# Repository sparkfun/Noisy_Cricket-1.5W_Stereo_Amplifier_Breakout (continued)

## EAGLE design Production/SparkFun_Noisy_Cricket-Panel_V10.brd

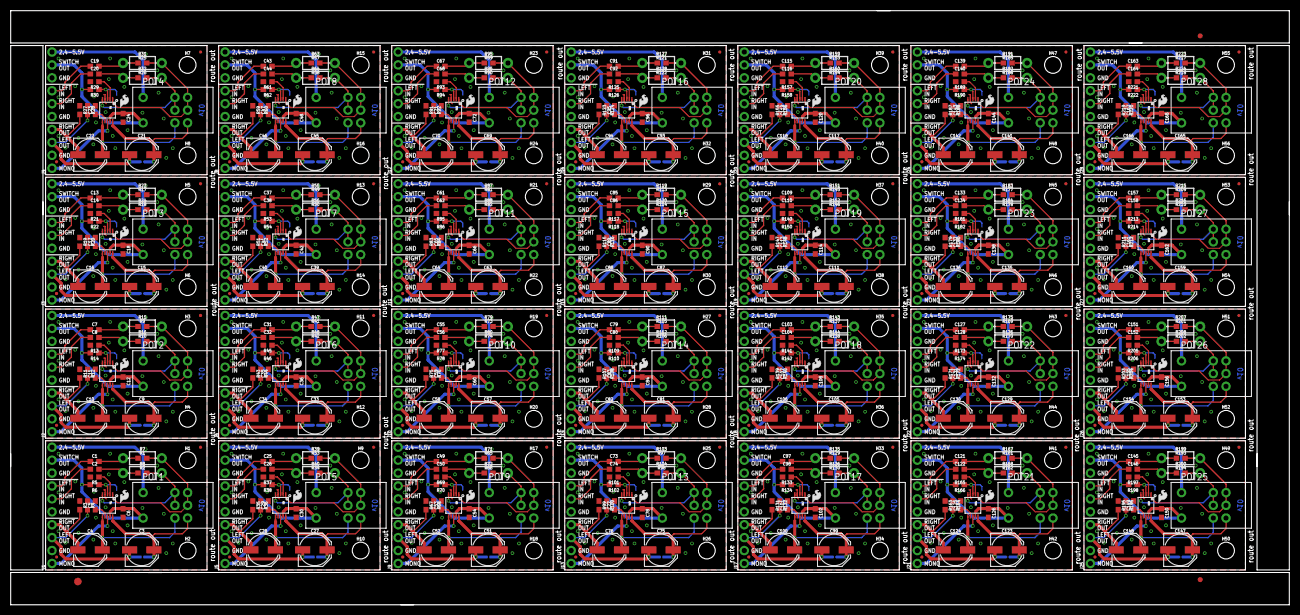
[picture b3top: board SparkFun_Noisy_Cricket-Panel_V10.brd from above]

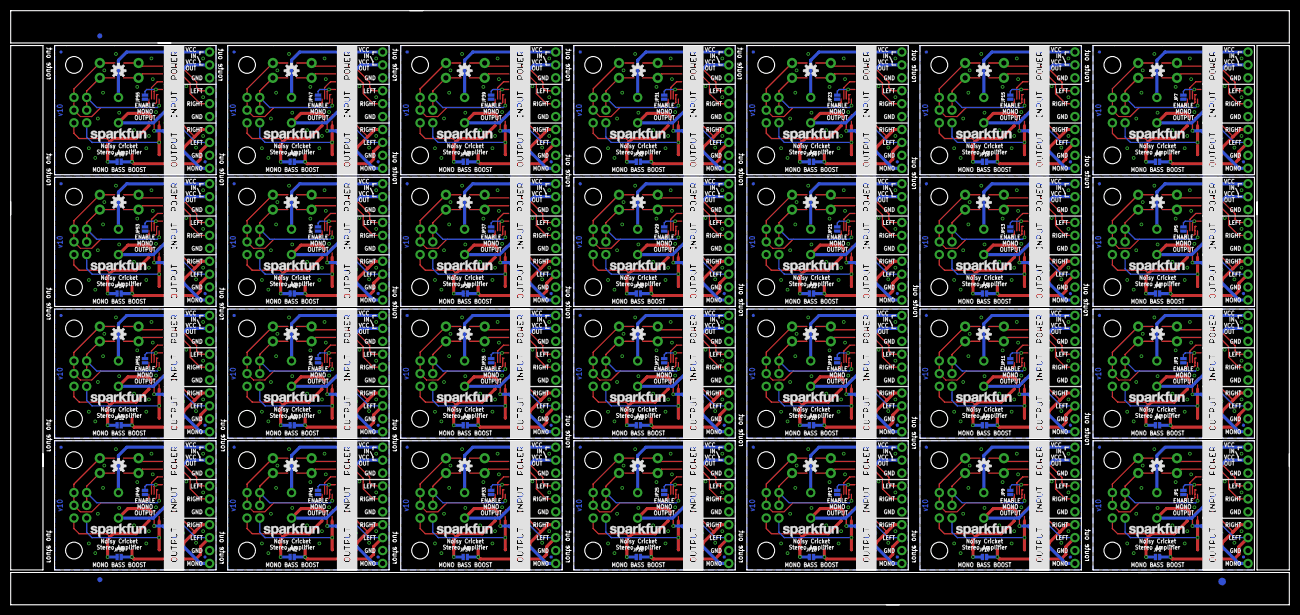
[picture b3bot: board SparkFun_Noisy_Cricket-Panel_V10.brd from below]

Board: 2 copper layers, 251.5 x 116.8 mm, 790 parts (171 on the bottom side), 476 nets.

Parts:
C1, C2, C5, C6, C7, C8, C11, C12, C13, C14, C17, C18, C19, C20, C23, C24, C25, C26, C29, C30, C31, C32, C35, C36, C37, C38, C41, C42, C43, C44, C47, C48, C49, C50, C53, C54, C55, C56, C59, C60, C61, C62, C65, C66, C67, C68, C71, C72, C73, C74, C77, C78, C79, C80, C83, C84, C85, C86, C89, C90, C91, C92, C95, C96, C97, C98, C101, C102, C103, C104, C107, C108, C109, C110, C113, C114, C115, C116, C119, C120, C121, C122, C125, C126, C127, C128, C131, C132, C133, C134, C137, C138, C139, C140, C143, C144, C145, C146, C149, C150, C151, C152, C155, C156, C157, C158, C161, C162, C163, C164, C167, C168: 1.0uF; 0603
C3, C4, C9, C10, C15, C16, C21, C22, C27, C28, C33, C34, C39, C40, C45, C46, C51, C52, C57, C58, C63, C64, C69, C70, C75, C76, C81, C82, C87, C88, C93, C94, C99, C100, C105, C106, C111, C112, C117, C118, C123, C124, C129, C130, C135, C136, C141, C142, C147, C148, C153, C154, C159, C160, C165, C166: 100uF; PANASONIC_D
E$1, E$2: FIDUCIAL-1.5X3
E$3, E$4, E$5, E$7: FIDUCIAL-1X2
FD1, FD2, FD3, FD4, FD5, FD6, FD7, FD8, FD9, FD10, FD11, FD12, FD13, FD14, FD15, FD16, FD17, FD18, FD19, FD20, FD21, FD22, FD23, FD24, FD25, FD26, FD27, FD28, FD29, FD30, FD31, FD32, FD33, FD34, FD35, FD36, FD37, FD38, FD39, FD40, FD41, FD42, FD43, FD44, FD45, FD46, FD47, FD48, FD49, FD50, FD51, FD52, FD53, FD54, FD55, FD56, FD57, FD58, FD59, FD60, FD61, FD62, FD63, FD64, FD65, FD66, FD67, FD68, FD69, FD70, FD71, FD72, FD73, FD74, FD75, FD76, FD77, FD78, FD79, FD80, FD81, FD82, FD83, FD84, FD85, FD86, FD87, FD88, FD89, FD90, FD91, FD92, FD93, FD94, FD95, FD96, FD97, FD98, FD99, FD100, FD101, FD102, FD103, FD104, FD105, FD106, FD107, FD108, FD109, FD110, FD111, FD112: FIDUCIALUFIDUCIAL; FIDUCIAL-MICRO
H1, H2, H3, H4, H5, H6, H7, H8, H9, H10, H11, H12, H13, H14, H15, H16, H17, H18, H19, H20, H21, H22, H23, H24, H25, H26, H27, H28, H29, H30, H31, H32, H33, H34, H35, H36, H37, H38, H39, H40, H41, H42, H43, H44, H45, H46, H47, H48, H49, H50, H51, H52, H53, H54, H55, H56: STAND-OFF
J1, J2, J3, J4, J5, J6, J7, J8, J9, J10, J11, J12, J13, J14, J15, J16, J17, J18, J19, J20, J21, J22, J23, J24, J25, J26, J27, J28: 1X10_NO_SILK
JP1, JP2, JP3, JP4, JP5, JP6, JP7, JP8, JP9, JP10, JP11, JP12, JP13, JP14, JP15, JP16, JP17, JP18, JP19, JP20, JP21, JP22, JP23, JP24, JP25, JP26, JP27, JP28, JP29, JP30, JP31, JP32, JP33, JP34, JP35, JP36, JP37, JP38, JP39, JP40, JP41, JP42, JP43, JP44, JP45, JP46, JP47, JP48, JP49, JP50, JP51, JP52, JP53, JP54, JP55, JP56: SMT-JUMPER_2_NO_NO-SILK
LOGO1, LOGO3, LOGO5, LOGO7, LOGO9, LOGO11, LOGO13, LOGO15, LOGO17, LOGO19, LOGO21, LOGO23, LOGO25, LOGO27, LOGO29, LOGO31, LOGO33, LOGO35, LOGO37, LOGO39, LOGO41, LOGO43, LOGO45, LOGO47, LOGO49, LOGO51, LOGO53, LOGO55: SFE_LOGO_NAME.1_INCH; SFE_LOGO_NAME_.1
LOGO2, LOGO4, LOGO6, LOGO8, LOGO10, LOGO12, LOGO14, LOGO16, LOGO18, LOGO20, LOGO22, LOGO24, LOGO26, LOGO28, LOGO30, LOGO32, LOGO34, LOGO36, LOGO38, LOGO40, LOGO42, LOGO44, LOGO46, LOGO48, LOGO50, LOGO52, LOGO54, LOGO56: OSHW-LOGOS; OSHW-LOGO-S
POT1, POT2, POT3, POT4, POT5, POT6, POT7, POT8, POT9, POT10, POT11, POT12, POT13, POT14, POT15, POT16, POT17, POT18, POT19, POT20, POT21, POT22, POT23, POT24, POT25, POT26, POT27, POT28: 20k; POT-DUAL-SWITCH-PTH
R1, R2, R9, R10, R17, R18, R25, R26, R33, R34, R41, R42, R49, R50, R57, R58, R65, R66, R73, R74, R81, R82, R89, R90, R97, R98, R105, R106, R113, R114, R121, R122, R129, R130, R137, R138, R145, R146, R153, R154, R161, R162, R169, R170, R177, R178, R185, R186, R193, R194, R201, R202, R209, R210, R217, R218: 2.2k; 0603
R3, R4, R11, R12, R19, R20, R27, R28, R35, R36, R43, R44, R51, R52, R59, R60, R67, R68, R75, R76, R83, R84, R91, R92, R99, R100, R107, R108, R115, R116, R123, R124, R131, R132, R139, R140, R147, R148, R155, R156, R163, R164, R171, R172, R179, R180, R187, R188, R195, R196, R203, R204, R211, R212, R219, R220: 1k; 0603
R5, R6, R13, R14, R21, R22, R29, R30, R37, R38, R45, R46, R53, R54, R61, R62, R69, R70, R77, R78, R85, R86, R93, R94, R101, R102, R109, R110, R117, R118, R125, R126, R133, R134, R141, R142, R149, R150, R157, R158, R165, R166, R173, R174, R181, R182, R189, R190, R197, R198, R205, R206, R213, R214, R221, R222: 100k; 0603
R7, R8, R15, R16, R23, R24, R31, R32, R39, R40, R47, R48, R55, R56, R63, R64, R71, R72, R79, R80, R87, R88, R95, R96, R103, R104, R111, R112, R119, R120, R127, R128, R135, R136, R143, R144, R151, R152, R159, R160, R167, R168, R175, R176, R183, R184, R191, R192, R199, R200, R207, R208, R215, R216, R223, R224: AXIAL-0.3-KIT
U1, U2, U3, U4, U5, U6, U7, U8, U9, U10, U11, U12, U13, U14, U15, U16, U17, U18, U19, U20, U21, U22, U23, U24, U25, U26, U27, U28: LM4853; TFSOP-10
U$1, U$2, U$3, U$4, U$5, U$6, U$7, U$8, U$9, U$10, U$11, U$12, U$13, U$14, U$15, U$16, U$17, U$18, U$19, U$20, U$21, U$22, U$23, U$24, U$25, U$26, U$27, U$28: SFE_LOGO_FLAME_.1

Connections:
5V: C6.1, J1.9, POT1.SW2, R6.2, U1.VDD
5V1: C12.1, J2.9, POT2.SW2, R14.2, U2.VDD
5V2: C18.1, J3.9, POT3.SW2, R22.2, U3.VDD
5V3: C24.1, J4.9, POT4.SW2, R30.2, U4.VDD
5V4: C30.1, J5.9, POT5.SW2, R38.2, U5.VDD
5V5: C36.1, J6.9, POT6.SW2, R46.2, U6.VDD
5V6: C42.1, J7.9, POT7.SW2, R54.2, U7.VDD
5V7: C48.1, J8.9, POT8.SW2, R62.2, U8.VDD
5V8: C54.1, J9.9, POT9.SW2, R70.2, U9.VDD
5V9: C60.1, J10.9, POT10.SW2, R78.2, U10.VDD
5V10: C66.1, J11.9, POT11.SW2, R86.2, U11.VDD
5V11: C72.1, J12.9, POT12.SW2, R94.2, U12.VDD
5V12: C78.1, J13.9, POT13.SW2, R102.2, U13.VDD
5V13: C84.1, J14.9, POT14.SW2, R110.2, U14.VDD
5V14: C90.1, J15.9, POT15.SW2, R118.2, U15.VDD
5V15: C96.1, J16.9, POT16.SW2, R126.2, U16.VDD
5V16: C102.1, J17.9, POT17.SW2, R134.2, U17.VDD
5V17: C108.1, J18.9, POT18.SW2, R142.2, U18.VDD
5V18: C114.1, J19.9, POT19.SW2, R150.2, U19.VDD
5V19: C120.1, J20.9, POT20.SW2, R158.2, U20.VDD
5V20: C126.1, J21.9, POT21.SW2, R166.2, U21.VDD
5V21: C132.1, J22.9, POT22.SW2, R174.2, U22.VDD
5V22: C138.1, J23.9, POT23.SW2, R182.2, U23.VDD
5V23: C144.1, J24.9, POT24.SW2, R190.2, U24.VDD
5V24: C150.1, J25.9, POT25.SW2, R198.2, U25.VDD
5V25: C156.1, J26.9, POT26.SW2, R206.2, U26.VDD
5V26: C162.1, J27.9, POT27.SW2, R214.2, U27.VDD
5V27: C168.1, J28.9, POT28.SW2, R222.2, U28.VDD
GND: C5.2, C6.2, J1.2, J1.5, J1.8, JP1.1, R3.1, R4.1, R5.2, U1.GND
GND1: C11.2, C12.2, J2.2, J2.5, J2.8, JP3.1, R11.1, R12.1, R13.2, U2.GND
GND2: C17.2, C18.2, J3.2, J3.5, J3.8, JP5.1, R19.1, R20.1, R21.2, U3.GND
GND3: C23.2, C24.2, J4.2, J4.5, J4.8, JP7.1, R27.1, R28.1, R29.2, U4.GND
GND4: C29.2, C30.2, J5.2, J5.5, J5.8, JP9.1, R35.1, R36.1, R37.2, U5.GND
GND5: C35.2, C36.2, J6.2, J6.5, J6.8, JP11.1, R43.1, R44.1, R45.2, U6.GND
GND6: C41.2, C42.2, J7.2, J7.5, J7.8, JP13.1, R51.1, R52.1, R53.2, U7.GND
GND7: C47.2, C48.2, J8.2, J8.5, J8.8, JP15.1, R59.1, R60.1, R61.2, U8.GND
GND8: C53.2, C54.2, J9.2, J9.5, J9.8, JP17.1, R67.1, R68.1, R69.2, U9.GND
GND9: C59.2, C60.2, J10.2, J10.5, J10.8, JP19.1, R75.1, R76.1, R77.2, U10.GND
GND10: C65.2, C66.2, J11.2, J11.5, J11.8, JP21.1, R83.1, R84.1, R85.2, U11.GND
GND11: C71.2, C72.2, J12.2, J12.5, J12.8, JP23.1, R91.1, R92.1, R93.2, U12.GND
GND12: C77.2, C78.2, J13.2, J13.5, J13.8, JP25.1, R99.1, R100.1, R101.2, U13.GND
GND13: C83.2, C84.2, J14.2, J14.5, J14.8, JP27.1, R107.1, R108.1, R109.2, U14.GND
GND14: C89.2, C90.2, J15.2, J15.5, J15.8, JP29.1, R115.1, R116.1, R117.2, U15.GND
GND15: C95.2, C96.2, J16.2, J16.5, J16.8, JP31.1, R123.1, R124.1, R125.2, U16.GND
GND16: C101.2, C102.2, J17.2, J17.5, J17.8, JP33.1, R131.1, R132.1, R133.2, U17.GND
GND17: C107.2, C108.2, J18.2, J18.5, J18.8, JP35.1, R139.1, R140.1, R141.2, U18.GND
GND18: C113.2, C114.2, J19.2, J19.5, J19.8, JP37.1, R147.1, R148.1, R149.2, U19.GND
GND19: C119.2, C120.2, J20.2, J20.5, J20.8, JP39.1, R155.1, R156.1, R157.2, U20.GND
GND20: C125.2, C126.2, J21.2, J21.5, J21.8, JP41.1, R163.1, R164.1, R165.2, U21.GND
GND21: C131.2, C132.2, J22.2, J22.5, J22.8, JP43.1, R171.1, R172.1, R173.2, U22.GND
GND22: C137.2, C138.2, J23.2, J23.5, J23.8, JP45.1, R179.1, R180.1, R181.2, U23.GND
GND23: C143.2, C144.2, J24.2, J24.5, J24.8, JP47.1, R187.1, R188.1, R189.2, U24.GND
GND24: C149.2, C150.2, J25.2, J25.5, J25.8, JP49.1, R195.1, R196.1, R197.2, U25.GND
GND25: C155.2, C156.2, J26.2, J26.5, J26.8, JP51.1, R203.1, R204.1, R205.2, U26.GND
GND26: C161.2, C162.2, J27.2, J27.5, J27.8, JP53.1, R211.1, R212.1, R213.2, U27.GND
GND27: C167.2, C168.2, J28.2, J28.5, J28.8, JP55.1, R219.1, R220.1, R221.2, U28.GND
LIN: C1.1, J1.7
LIN1: C7.1, J2.7
LIN2: C13.1, J3.7
LIN3: C19.1, J4.7
LIN4: C25.1, J5.7
LIN5: C31.1, J6.7
LIN6: C37.1, J7.7
LIN7: C43.1, J8.7
LIN8: C49.1, J9.7
LIN9: C55.1, J10.7
LIN10: C61.1, J11.7
LIN11: C67.1, J12.7
LIN12: C73.1, J13.7
LIN13: C79.1, J14.7
LIN14: C85.1, J15.7
LIN15: C91.1, J16.7
LIN16: C97.1, J17.7
LIN17: C103.1, J18.7
LIN18: C109.1, J19.7
LIN19: C115.1, J20.7
LIN20: C121.1, J21.7
LIN21: C127.1, J22.7
LIN22: C133.1, J23.7
LIN23: C139.1, J24.7
LIN24: C145.1, J25.7
LIN25: C151.1, J26.7
LIN26: C157.1, J27.7
LIN27: C163.1, J28.7
LOUT: C3.-, J1.3, JP2.2, R4.2
LOUT1: C9.-, J2.3, JP4.2, R12.2
LOUT2: C15.-, J3.3, JP6.2, R20.2
LOUT3: C21.-, J4.3, JP8.2, R28.2
LOUT4: C27.-, J5.3, JP10.2, R36.2
LOUT5: C33.-, J6.3, JP12.2, R44.2
LOUT6: C39.-, J7.3, JP14.2, R52.2
LOUT7: C45.-, J8.3, JP16.2, R60.2
LOUT8: C51.-, J9.3, JP18.2, R68.2
LOUT9: C57.-, J10.3, JP20.2, R76.2
LOUT10: C63.-, J11.3, JP22.2, R84.2
LOUT11: C69.-, J12.3, JP24.2, R92.2
LOUT12: C75.-, J13.3, JP26.2, R100.2
LOUT13: C81.-, J14.3, JP28.2, R108.2
LOUT14: C87.-, J15.3, JP30.2, R116.2
LOUT15: C93.-, J16.3, JP32.2, R124.2
LOUT16: C99.-, J17.3, JP34.2, R132.2
LOUT17: C105.-, J18.3, JP36.2, R140.2
LOUT18: C111.-, J19.3, JP38.2, R148.2
LOUT19: C117.-, J20.3, JP40.2, R156.2
LOUT20: C123.-, J21.3, JP42.2, R164.2
LOUT21: C129.-, J22.3, JP44.2, R172.2
LOUT22: C135.-, J23.3, JP46.2, R180.2
LOUT23: C141.-, J24.3, JP48.2, R188.2
LOUT24: C147.-, J25.3, JP50.2, R196.2
LOUT25: C153.-, J26.3, JP52.2, R204.2
LOUT26: C159.-, J27.3, JP54.2, R212.2
LOUT27: C165.-, J28.3, JP56.2, R220.2
LOUT+: C3.+, JP2.1, POT1.A3, U1.LOUT
LOUT+1: C9.+, JP4.1, POT2.A3, U2.LOUT
LOUT+2: C15.+, JP6.1, POT3.A3, U3.LOUT
LOUT+3: C21.+, JP8.1, POT4.A3, U4.LOUT
LOUT+4: C27.+, JP10.1, POT5.A3, U5.LOUT
LOUT+5: C33.+, JP12.1, POT6.A3, U6.LOUT
LOUT+6: C39.+, JP14.1, POT7.A3, U7.LOUT
LOUT+7: C45.+, JP16.1, POT8.A3, U8.LOUT
LOUT+8: C51.+, JP18.1, POT9.A3, U9.LOUT
LOUT+9: C57.+, JP20.1, POT10.A3, U10.LOUT
LOUT+10: C63.+, JP22.1, POT11.A3, U11.LOUT
LOUT+11: C69.+, JP24.1, POT12.A3, U12.LOUT
LOUT+12: C75.+, JP26.1, POT13.A3, U13.LOUT
LOUT+13: C81.+, JP28.1, POT14.A3, U14.LOUT
LOUT+14: C87.+, JP30.1, POT15.A3, U15.LOUT
LOUT+15: C93.+, JP32.1, POT16.A3, U16.LOUT
LOUT+16: C99.+, JP34.1, POT17.A3, U17.LOUT
LOUT+17: C105.+, JP36.1, POT18.A3, U18.LOUT
LOUT+18: C111.+, JP38.1, POT19.A3, U19.LOUT
LOUT+19: C117.+, JP40.1, POT20.A3, U20.LOUT
LOUT+20: C123.+, JP42.1, POT21.A3, U21.LOUT
LOUT+21: C129.+, JP44.1, POT22.A3, U22.LOUT
LOUT+22: C135.+, JP46.1, POT23.A3, U23.LOUT
LOUT+23: C141.+, JP48.1, POT24.A3, U24.LOUT
LOUT+24: C147.+, JP50.1, POT25.A3, U25.LOUT
LOUT+25: C153.+, JP52.1, POT26.A3, U26.LOUT
LOUT+26: C159.+, JP54.1, POT27.A3, U27.LOUT
LOUT+27: C165.+, JP56.1, POT28.A3, U28.LOUT
MODE: JP1.2, R6.1, U1.HP-IN
MODE1: JP3.2, R14.1, U2.HP-IN
MODE2: JP5.2, R22.1, U3.HP-IN
MODE3: JP7.2, R30.1, U4.HP-IN
MODE4: JP9.2, R38.1, U5.HP-IN
MODE5: JP11.2, R46.1, U6.HP-IN
MODE6: JP13.2, R54.1, U7.HP-IN
MODE7: JP15.2, R62.1, U8.HP-IN
MODE8: JP17.2, R70.1, U9.HP-IN
MODE9: JP19.2, R78.1, U10.HP-IN
MODE10: JP21.2, R86.1, U11.HP-IN
MODE11: JP23.2, R94.1, U12.HP-IN
MODE12: JP25.2, R102.1, U13.HP-IN
MODE13: JP27.2, R110.1, U14.HP-IN
MODE14: JP29.2, R118.1, U15.HP-IN
MODE15: JP31.2, R126.1, U16.HP-IN
MODE16: JP33.2, R134.1, U17.HP-IN
MODE17: JP35.2, R142.1, U18.HP-IN
MODE18: JP37.2, R150.1, U19.HP-IN
MODE19: JP39.2, R158.1, U20.HP-IN
MODE20: JP41.2, R166.1, U21.HP-IN
MODE21: JP43.2, R174.1, U22.HP-IN
MODE22: JP45.2, R182.1, U23.HP-IN
MODE23: JP47.2, R190.1, U24.HP-IN
MODE24: JP49.2, R198.1, U25.HP-IN
MODE25: JP51.2, R206.1, U26.HP-IN
MODE26: JP53.2, R214.1, U27.HP-IN
MODE27: JP55.2, R222.1, U28.HP-IN
MONO_OUT: J1.1, U1.BTL
MONO_OUT1: J2.1, U2.BTL
MONO_OUT2: J3.1, U3.BTL
MONO_OUT3: J4.1, U4.BTL
MONO_OUT4: J5.1, U5.BTL
MONO_OUT5: J6.1, U6.BTL
MONO_OUT6: J7.1, U7.BTL
MONO_OUT7: J8.1, U8.BTL
MONO_OUT8: J9.1, U9.BTL
MONO_OUT9: J10.1, U10.BTL
MONO_OUT10: J11.1, U11.BTL
MONO_OUT11: J12.1, U12.BTL
MONO_OUT12: J13.1, U13.BTL
MONO_OUT13: J14.1, U14.BTL
MONO_OUT14: J15.1, U15.BTL
MONO_OUT15: J16.1, U16.BTL
MONO_OUT16: J17.1, U17.BTL
MONO_OUT17: J18.1, U18.BTL
MONO_OUT18: J19.1, U19.BTL
MONO_OUT19: J20.1, U20.BTL
MONO_OUT20: J21.1, U21.BTL
MONO_OUT21: J22.1, U22.BTL
MONO_OUT22: J23.1, U23.BTL
MONO_OUT23: J24.1, U24.BTL
MONO_OUT24: J25.1, U25.BTL
MONO_OUT25: J26.1, U26.BTL
MONO_OUT26: J27.1, U27.BTL
MONO_OUT27: J28.1, U28.BTL
unnamed: C7.2, R9.1, R15.P$1
unnamed: R13.1, U2.SDN
unnamed: C1.2, R1.1, R7.P$1
unnamed: C11.1, U2.BP
unnamed: C5.1, U1.BP
unnamed: C2.2, R2.1, R8.P$1
unnamed: C10.+, POT2.B3, U2.ROUT
unnamed: POT2.A1, POT2.A2, R9.2, R15.P$2, U2.LIN
unnamed: R5.1, U1.SDN
unnamed: POT2.B1, POT2.B2, R10.2, R16.P$2, U2.RIN
unnamed: C8.2, R10.1, R16.P$1
unnamed: C4.+, POT1.B3, U1.ROUT
unnamed: C13.2, R17.1, R23.P$1
unnamed: R21.1, U3.SDN
unnamed: C17.1, U3.BP
unnamed: C16.+, POT3.B3, U3.ROUT
unnamed: POT3.A1, POT3.A2, R17.2, R23.P$2, U3.LIN
unnamed: POT3.B1, POT3.B2, R18.2, R24.P$2, U3.RIN
unnamed: C14.2, R18.1, R24.P$1
unnamed: C19.2, R25.1, R31.P$1
unnamed: POT1.A1, POT1.A2, R1.2, R7.P$2, U1.LIN
unnamed: R29.1, U4.SDN
unnamed: C23.1, U4.BP
unnamed: POT1.B1, POT1.B2, R2.2, R8.P$2, U1.RIN
unnamed: C22.+, POT4.B3, U4.ROUT
unnamed: POT4.A1, POT4.A2, R25.2, R31.P$2, U4.LIN
unnamed: POT4.B1, POT4.B2, R26.2, R32.P$2, U4.RIN
unnamed: C20.2, R26.1, R32.P$1
unnamed: C25.2, R33.1, R39.P$1
unnamed: R37.1, U5.SDN
unnamed: C29.1, U5.BP
unnamed: C28.+, POT5.B3, U5.ROUT
unnamed: POT5.A1, POT5.A2, R33.2, R39.P$2, U5.LIN
unnamed: POT5.B1, POT5.B2, R34.2, R40.P$2, U5.RIN
unnamed: C26.2, R34.1, R40.P$1
unnamed: C31.2, R41.1, R47.P$1
unnamed: R45.1, U6.SDN
unnamed: C35.1, U6.BP
unnamed: C34.+, POT6.B3, U6.ROUT
unnamed: POT6.A1, POT6.A2, R41.2, R47.P$2, U6.LIN
unnamed: POT6.B1, POT6.B2, R42.2, R48.P$2, U6.RIN
unnamed: C32.2, R42.1, R48.P$1
unnamed: C37.2, R49.1, R55.P$1
unnamed: R53.1, U7.SDN
unnamed: C41.1, U7.BP
unnamed: C40.+, POT7.B3, U7.ROUT
unnamed: POT7.A1, POT7.A2, R49.2, R55.P$2, U7.LIN
unnamed: POT7.B1, POT7.B2, R50.2, R56.P$2, U7.RIN
unnamed: C38.2, R50.1, R56.P$1
unnamed: C43.2, R57.1, R63.P$1
unnamed: R61.1, U8.SDN
unnamed: C47.1, U8.BP
unnamed: C46.+, POT8.B3, U8.ROUT
unnamed: POT8.A1, POT8.A2, R57.2, R63.P$2, U8.LIN
unnamed: POT8.B1, POT8.B2, R58.2, R64.P$2, U8.RIN
unnamed: C44.2, R58.1, R64.P$1
unnamed: C49.2, R65.1, R71.P$1
unnamed: R69.1, U9.SDN
unnamed: C53.1, U9.BP
unnamed: C52.+, POT9.B3, U9.ROUT
unnamed: POT9.A1, POT9.A2, R65.2, R71.P$2, U9.LIN
unnamed: POT9.B1, POT9.B2, R66.2, R72.P$2, U9.RIN
unnamed: C50.2, R66.1, R72.P$1
unnamed: C55.2, R73.1, R79.P$1
unnamed: R77.1, U10.SDN
unnamed: C59.1, U10.BP
unnamed: C58.+, POT10.B3, U10.ROUT
unnamed: POT10.A1, POT10.A2, R73.2, R79.P$2, U10.LIN
unnamed: POT10.B1, POT10.B2, R74.2, R80.P$2, U10.RIN
unnamed: C56.2, R74.1, R80.P$1
unnamed: C61.2, R81.1, R87.P$1
unnamed: R85.1, U11.SDN
unnamed: C65.1, U11.BP
unnamed: C64.+, POT11.B3, U11.ROUT
unnamed: POT11.A1, POT11.A2, R81.2, R87.P$2, U11.LIN
unnamed: POT11.B1, POT11.B2, R82.2, R88.P$2, U11.RIN
unnamed: C62.2, R82.1, R88.P$1
unnamed: C67.2, R89.1, R95.P$1
unnamed: R93.1, U12.SDN
unnamed: C71.1, U12.BP
unnamed: C70.+, POT12.B3, U12.ROUT
unnamed: POT12.A1, POT12.A2, R89.2, R95.P$2, U12.LIN
unnamed: POT12.B1, POT12.B2, R90.2, R96.P$2, U12.RIN
unnamed: C68.2, R90.1, R96.P$1
unnamed: C73.2, R97.1, R103.P$1
unnamed: R101.1, U13.SDN
unnamed: C77.1, U13.BP
unnamed: C76.+, POT13.B3, U13.ROUT
unnamed: POT13.A1, POT13.A2, R97.2, R103.P$2, U13.LIN
unnamed: POT13.B1, POT13.B2, R98.2, R104.P$2, U13.RIN
unnamed: C74.2, R98.1, R104.P$1
unnamed: C79.2, R105.1, R111.P$1
unnamed: R109.1, U14.SDN
unnamed: C83.1, U14.BP
unnamed: C82.+, POT14.B3, U14.ROUT
unnamed: POT14.A1, POT14.A2, R105.2, R111.P$2, U14.LIN
unnamed: POT14.B1, POT14.B2, R106.2, R112.P$2, U14.RIN
unnamed: C80.2, R106.1, R112.P$1
unnamed: C85.2, R113.1, R119.P$1
unnamed: R117.1, U15.SDN
unnamed: C89.1, U15.BP
unnamed: C88.+, POT15.B3, U15.ROUT
unnamed: POT15.A1, POT15.A2, R113.2, R119.P$2, U15.LIN
unnamed: POT15.B1, POT15.B2, R114.2, R120.P$2, U15.RIN
unnamed: C86.2, R114.1, R120.P$1
unnamed: C91.2, R121.1, R127.P$1
unnamed: R125.1, U16.SDN
unnamed: C95.1, U16.BP
unnamed: C94.+, POT16.B3, U16.ROUT
unnamed: POT16.A1, POT16.A2, R121.2, R127.P$2, U16.LIN
unnamed: POT16.B1, POT16.B2, R122.2, R128.P$2, U16.RIN
unnamed: C92.2, R122.1, R128.P$1
unnamed: C97.2, R129.1, R135.P$1
unnamed: R133.1, U17.SDN
unnamed: C101.1, U17.BP
unnamed: C100.+, POT17.B3, U17.ROUT
unnamed: POT17.A1, POT17.A2, R129.2, R135.P$2, U17.LIN
unnamed: POT17.B1, POT17.B2, R130.2, R136.P$2, U17.RIN
unnamed: C98.2, R130.1, R136.P$1
unnamed: C103.2, R137.1, R143.P$1
unnamed: R141.1, U18.SDN
unnamed: C107.1, U18.BP
unnamed: C106.+, POT18.B3, U18.ROUT
unnamed: POT18.A1, POT18.A2, R137.2, R143.P$2, U18.LIN
unnamed: POT18.B1, POT18.B2, R138.2, R144.P$2, U18.RIN
unnamed: C104.2, R138.1, R144.P$1
unnamed: C109.2, R145.1, R151.P$1
unnamed: R149.1, U19.SDN
unnamed: C113.1, U19.BP
unnamed: C112.+, POT19.B3, U19.ROUT
unnamed: POT19.A1, POT19.A2, R145.2, R151.P$2, U19.LIN
unnamed: POT19.B1, POT19.B2, R146.2, R152.P$2, U19.RIN
unnamed: C110.2, R146.1, R152.P$1
unnamed: C115.2, R153.1, R159.P$1
unnamed: R157.1, U20.SDN
unnamed: C119.1, U20.BP
unnamed: C118.+, POT20.B3, U20.ROUT
unnamed: POT20.A1, POT20.A2, R153.2, R159.P$2, U20.LIN
unnamed: POT20.B1, POT20.B2, R154.2, R160.P$2, U20.RIN
unnamed: C116.2, R154.1, R160.P$1
unnamed: C121.2, R161.1, R167.P$1
unnamed: R165.1, U21.SDN
unnamed: C125.1, U21.BP
unnamed: C124.+, POT21.B3, U21.ROUT
unnamed: POT21.A1, POT21.A2, R161.2, R167.P$2, U21.LIN
unnamed: POT21.B1, POT21.B2, R162.2, R168.P$2, U21.RIN
unnamed: C122.2, R162.1, R168.P$1
unnamed: C127.2, R169.1, R175.P$1
unnamed: R173.1, U22.SDN
unnamed: C131.1, U22.BP
unnamed: C130.+, POT22.B3, U22.ROUT
unnamed: POT22.A1, POT22.A2, R169.2, R175.P$2, U22.LIN
unnamed: POT22.B1, POT22.B2, R170.2, R176.P$2, U22.RIN
unnamed: C128.2, R170.1, R176.P$1
unnamed: C133.2, R177.1, R183.P$1
unnamed: R181.1, U23.SDN
unnamed: C137.1, U23.BP
unnamed: C136.+, POT23.B3, U23.ROUT
unnamed: POT23.A1, POT23.A2, R177.2, R183.P$2, U23.LIN
unnamed: POT23.B1, POT23.B2, R178.2, R184.P$2, U23.RIN
unnamed: C134.2, R178.1, R184.P$1
unnamed: C139.2, R185.1, R191.P$1
unnamed: R189.1, U24.SDN
unnamed: C143.1, U24.BP
unnamed: C142.+, POT24.B3, U24.ROUT
unnamed: POT24.A1, POT24.A2, R185.2, R191.P$2, U24.LIN
unnamed: POT24.B1, POT24.B2, R186.2, R192.P$2, U24.RIN
unnamed: C140.2, R186.1, R192.P$1
unnamed: C145.2, R193.1, R199.P$1
unnamed: R197.1, U25.SDN
unnamed: C149.1, U25.BP
unnamed: C148.+, POT25.B3, U25.ROUT
unnamed: POT25.A1, POT25.A2, R193.2, R199.P$2, U25.LIN
unnamed: POT25.B1, POT25.B2, R194.2, R200.P$2, U25.RIN
unnamed: C146.2, R194.1, R200.P$1
unnamed: C151.2, R201.1, R207.P$1
unnamed: R205.1, U26.SDN
unnamed: C155.1, U26.BP
unnamed: C154.+, POT26.B3, U26.ROUT
unnamed: POT26.A1, POT26.A2, R201.2, R207.P$2, U26.LIN
unnamed: POT26.B1, POT26.B2, R202.2, R208.P$2, U26.RIN
unnamed: C152.2, R202.1, R208.P$1
unnamed: C157.2, R209.1, R215.P$1
unnamed: R213.1, U27.SDN
unnamed: C161.1, U27.BP
unnamed: C160.+, POT27.B3, U27.ROUT
unnamed: POT27.A1, POT27.A2, R209.2, R215.P$2, U27.LIN
unnamed: POT27.B1, POT27.B2, R210.2, R216.P$2, U27.RIN
unnamed: C158.2, R210.1, R216.P$1
unnamed: C163.2, R217.1, R223.P$1
unnamed: R221.1, U28.SDN
unnamed: C167.1, U28.BP
unnamed: C166.+, POT28.B3, U28.ROUT
unnamed: POT28.A1, POT28.A2, R217.2, R223.P$2, U28.LIN
unnamed: POT28.B1, POT28.B2, R218.2, R224.P$2, U28.RIN
unnamed: C164.2, R218.1, R224.P$1
RIN: C2.1, J1.6
RIN1: C8.1, J2.6
RIN2: C14.1, J3.6
RIN3: C20.1, J4.6
RIN4: C26.1, J5.6
RIN5: C32.1, J6.6
RIN6: C38.1, J7.6
RIN7: C44.1, J8.6
RIN8: C50.1, J9.6
RIN9: C56.1, J10.6
RIN10: C62.1, J11.6
RIN11: C68.1, J12.6
RIN12: C74.1, J13.6
RIN13: C80.1, J14.6
RIN14: C86.1, J15.6
RIN15: C92.1, J16.6
RIN16: C98.1, J17.6
RIN17: C104.1, J18.6
RIN18: C110.1, J19.6
RIN19: C116.1, J20.6
RIN20: C122.1, J21.6
RIN21: C128.1, J22.6
RIN22: C134.1, J23.6
RIN23: C140.1, J24.6
RIN24: C146.1, J25.6
RIN25: C152.1, J26.6
RIN26: C158.1, J27.6
RIN27: C164.1, J28.6
ROUT: C4.-, J1.4, R3.2
ROUT1: C10.-, J2.4, R11.2
ROUT2: C16.-, J3.4, R19.2
ROUT3: C22.-, J4.4, R27.2
ROUT4: C28.-, J5.4, R35.2
ROUT5: C34.-, J6.4, R43.2
ROUT6: C40.-, J7.4, R51.2
ROUT7: C46.-, J8.4, R59.2
ROUT8: C52.-, J9.4, R67.2
ROUT9: C58.-, J10.4, R75.2
ROUT10: C64.-, J11.4, R83.2
ROUT11: C70.-, J12.4, R91.2
ROUT12: C76.-, J13.4, R99.2
ROUT13: C82.-, J14.4, R107.2
ROUT14: C88.-, J15.4, R115.2
ROUT15: C94.-, J16.4, R123.2
ROUT16: C100.-, J17.4, R131.2
ROUT17: C106.-, J18.4, R139.2
ROUT18: C112.-, J19.4, R147.2
ROUT19: C118.-, J20.4, R155.2
ROUT20: C124.-, J21.4, R163.2
ROUT21: C130.-, J22.4, R171.2
ROUT22: C136.-, J23.4, R179.2
ROUT23: C142.-, J24.4, R187.2
ROUT24: C148.-, J25.4, R195.2
ROUT25: C154.-, J26.4, R203.2
ROUT26: C160.-, J27.4, R211.2
ROUT27: C166.-, J28.4, R219.2
VIN: J1.10, POT1.SW1
VIN1: J2.10, POT2.SW1
VIN2: J3.10, POT3.SW1
VIN3: J4.10, POT4.SW1
VIN4: J5.10, POT5.SW1
VIN5: J6.10, POT6.SW1
VIN6: J7.10, POT7.SW1
VIN7: J8.10, POT8.SW1
VIN8: J9.10, POT9.SW1
VIN9: J10.10, POT10.SW1
VIN10: J11.10, POT11.SW1
VIN11: J12.10, POT12.SW1
VIN12: J13.10, POT13.SW1
VIN13: J14.10, POT14.SW1
VIN14: J15.10, POT15.SW1
VIN15: J16.10, POT16.SW1
VIN16: J17.10, POT17.SW1
VIN17: J18.10, POT18.SW1
VIN18: J19.10, POT19.SW1
VIN19: J20.10, POT20.SW1
VIN20: J21.10, POT21.SW1
VIN21: J22.10, POT22.SW1
VIN22: J23.10, POT23.SW1
VIN23: J24.10, POT24.SW1
VIN24: J25.10, POT25.SW1
VIN25: J26.10, POT26.SW1
VIN26: J27.10, POT27.SW1
VIN27: J28.10, POT28.SW1

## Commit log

2017-09-05 Initial Commit
    Added Eagles files for proto version 01
2017-09-26 Added PROD_ID to C12
2017-09-26 DFM Changes
    Added values missing on a few parts
2018-01-31 Updated board from Pocket Amp to Noisy Cricket
2018-02-02 Design Review Changes
    - Moved JP1 further away from POT1
    - Added JP2 to short C3 and increase bass frequency reponse in mono
    operation
2018-02-02 Corrected board position
    - Board was saved upside down, corrected by flipping board back around
    and resaving.
2018-02-27 v10 Changes
    - Replaced C1/C2 with X7R capacitors with a better low end frequency
    response.
    - Moved C3/C4 further away from POT1.
    - Replaced R1/R2 with 2.2k resistors instead of 20k.
    - Added lines to top silk to separate Power/Input/Output sections.
    - Changed "Mono Enable" silk on bottom layer to "Mono Output".
2018-02-27 v10 Changes cont.
    - New 1.0uF capacitors weren't added to previous commit. Added correct
    capacitors.
2018-02-27 Design Review Changes
    minor changes to silk after design review
2018-03-05 QC Fixes
    - Increased anular ring of pot from AUTO to 0.074".
    - Fixed schematic version number to 10.
2018-03-09 V10 panel
2018-03-09 moved to origin
2018-03-12 updated panel
    missing "route out"
2018-04-17 Added README
